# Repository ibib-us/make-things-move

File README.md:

# make-things-move
Create your own remote control robot from the ground up

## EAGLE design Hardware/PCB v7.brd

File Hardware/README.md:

# Hardware

This folder contains the latest schematic and layout of the featherwing for your robot.

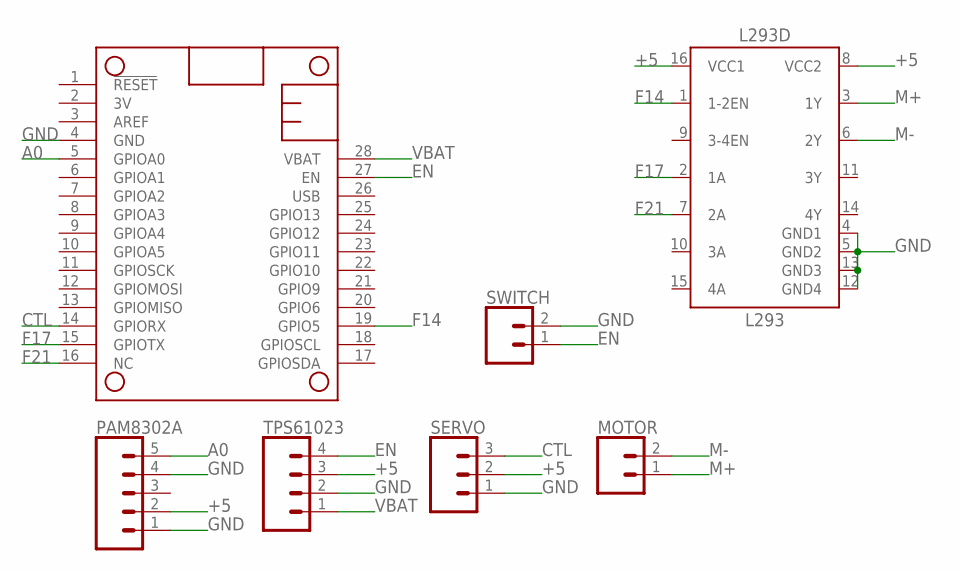
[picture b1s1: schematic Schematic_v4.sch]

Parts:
L293D: L293; DIP762W53P254L1969H508Q16B
MOTOR: CONN_02; 1X02
MS1: FEATHERWING_NODIM; FEATHERWING_DIM
PAM8302A: CONN_05; 1X05
SERVO: CONN_03; 1X03
SWITCH: CONN_02; 1X02
TPS61023: CONN_04; 1X04

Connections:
+5: L293D.8 (VCC2), L293D.16 (VCC1), PAM8302A.2, SERVO.2, TPS61023.3
A0: MS1.5 (GPIOA0), PAM8302A.5
CTL: MS1.14 (GPIORX), SERVO.3
EN: MS1.27 (EN), SWITCH.1, TPS61023.4
F14: L293D.1 (1-2EN), MS1.19 (GPIO5)
F17: L293D.2 (1A), MS1.15 (GPIOTX)
F21: L293D.7 (2A), MS1.16 (NC)
GND: L293D.4 (GND1), L293D.5 (GND2), L293D.12 (GND4), L293D.13 (GND3), MS1.4 (GND), PAM8302A.1, PAM8302A.4, SERVO.1, SWITCH.2, TPS61023.2
M+: L293D.3 (1Y), MOTOR.1
M-: L293D.6 (2Y), MOTOR.2
VBAT: MS1.28 (VBAT), TPS61023.1

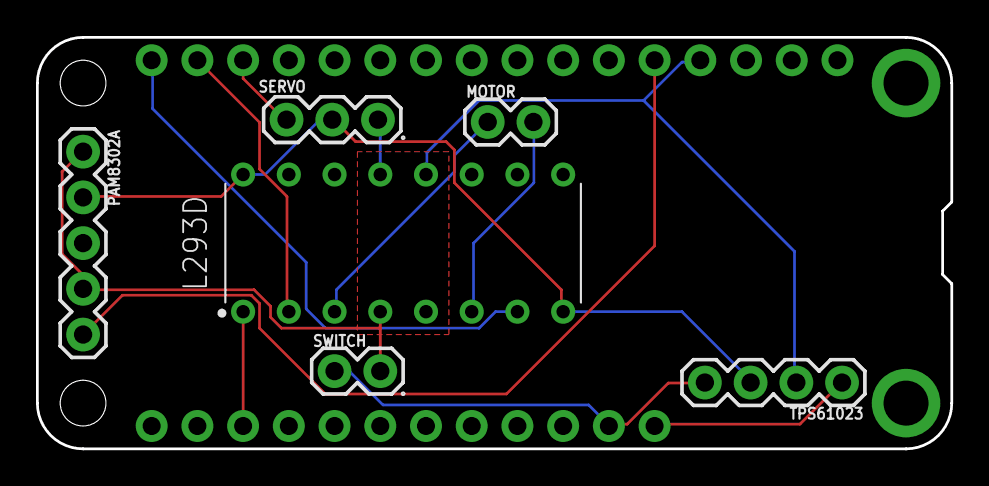
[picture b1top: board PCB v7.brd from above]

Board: 2 copper layers, 50.8 x 22.9 mm, 7 parts (0 on the bottom side), 11 nets.

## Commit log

2023-07-28 initial code
2023-07-29 update servo limits
2023-10-04 more content
2023-10-04 capital workaround a
2023-10-04 capital workaround b
2023-10-04 typos
2023-10-08 table problems
2023-10-08 test
2023-10-08 start
2023-10-08 formatting fixed?
2023-10-09 finished draft
2023-10-25 Code refactor for cleaner logging
2023-10-25 Fix audio flag name
2023-10-25 New and improved gamepad!
2023-10-25 Support for per-button custom callbacks
2023-10-27 Defined callbacks to move robot, added comments
2023-10-27 Refactored code for ease of maintenance
2023-10-29 Improvements and bug fixes from workshop
2023-10-29 Additional bugfix
2023-10-29 Improve debug logging
2023-10-29 Logic for debugging duty cycle settings
2023-10-31 Added hardware docs
2023-11-01 Add settings file
2023-11-01 Move servo duty settings to settings file

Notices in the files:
parts and their libraries:
SparkFun-Connectors: Licensing: Creative Commons ShareAlike 4.0 International - https://creativecommons.org/licenses/by-sa/4.0
